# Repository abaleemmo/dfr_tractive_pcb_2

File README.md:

This project was made in fall 2026. It was made for Dallas Formula Racing, The formula SAE team based at The University of Texas at Dallas. It was made as a part of the embedded onboarding. 

See Tractive System Status Indicator w_ two boards & firmware.pdf for the project definition.

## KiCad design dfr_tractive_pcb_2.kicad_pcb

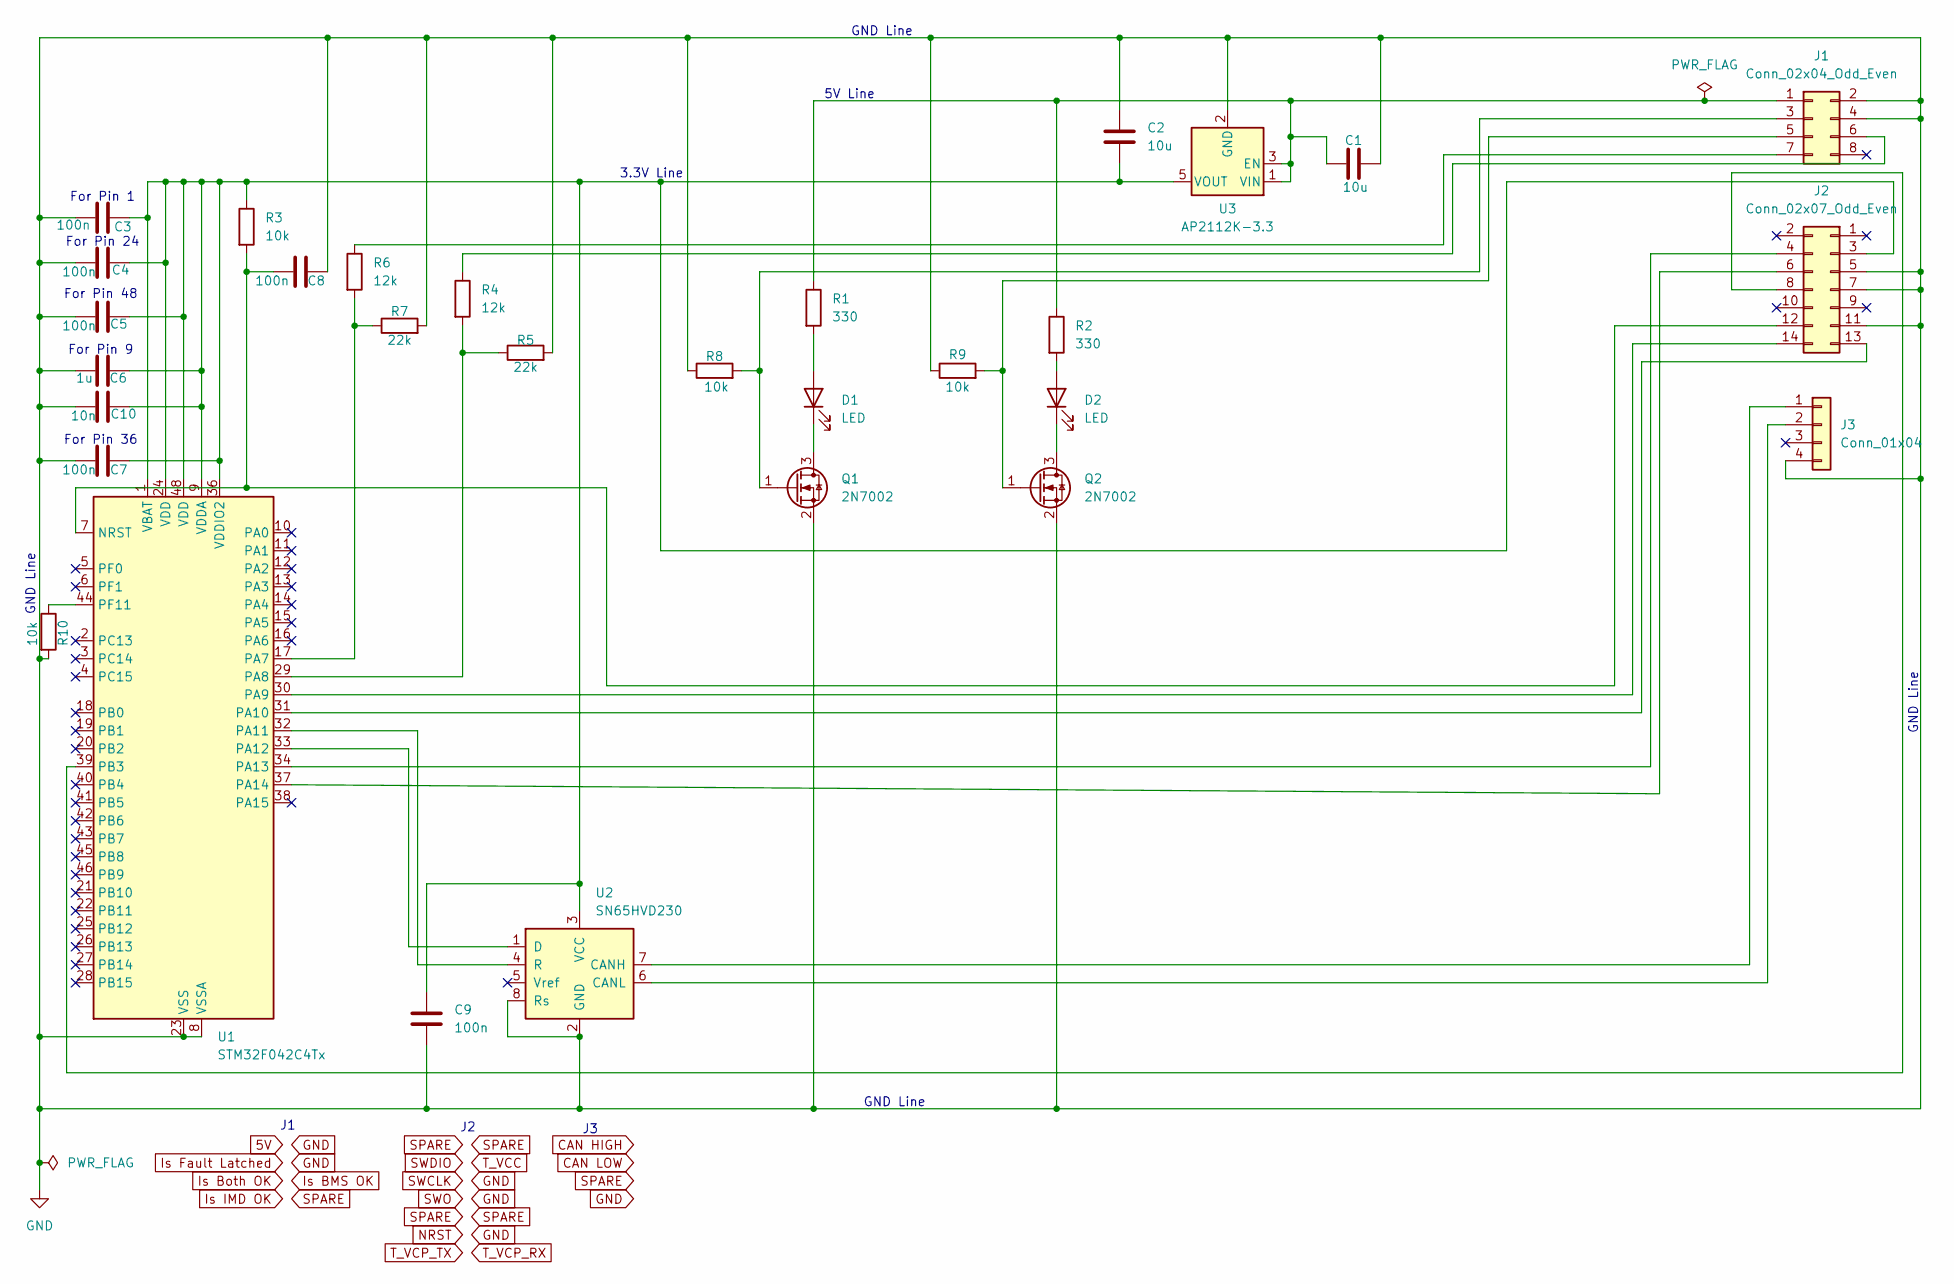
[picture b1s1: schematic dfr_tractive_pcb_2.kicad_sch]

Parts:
C1, C2: 10u; C_0805_2012Metric
C3, C4, C5, C7, C8, C9: 100n; C_0805_2012Metric
C6: 1u; C_0805_2012Metric
C10: 10n; C_0805_2012Metric
D1, D2: LED; LED_1206_3216Metric
J1: Conn_02x04_Odd_Even; PinSocket_2x04_P2.54mm_Vertical_SMD
J2: Conn_02x07_Odd_Even; SAMTEC_SHF-107-01-L-D-SM
J3: Conn_01x04; PinSocket_1x04_P2.54mm_Vertical_SMD_Pin1Right
Q1, Q2: 2N7002; SOT-23
R1, R2: 330; R_0805_2012Metric
R3, R8, R9, R10: 10k; R_0805_2012Metric
R4, R6: 12k; R_0805_2012Metric
R5, R7: 22k; R_0805_2012Metric
U1: STM32F042C4Tx; LQFP-48_7x7mm_P0.5mm
U2: SN65HVD230; SOIC-8_3.9x4.9mm_P1.27mm
U3: AP2112K-3.3; SOT-23-5

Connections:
GND: C1.1, C2.1, C3.2, C4.1, C5.1, C6.1, C7.2, C8.1, C9.2, C10.2, J1.2, J1.4, J2.5, J2.7, J2.11, J3.4, Q1.2 (S), Q2.2 (S), R5.2, R7.2, R8.1, R9.1, R10.2, U1.8 (VSSA), U1.23 (VSS), U1.35 (VSS), U1.47 (VSS), U2.2 (GND), U2.8 (Rs), U3.2 (GND)
unnamed: D1.2 (A), R1.2
unnamed: D1.1 (K), Q1.3 (D)
unnamed: D2.2 (A), R2.2
unnamed: D2.1 (K), Q2.3 (D)
unnamed: C1.2, J1.1, R1.1, R2.1, U3.1 (VIN), U3.3 (EN)
unnamed: J1.3, Q1.1 (G), R8.2
unnamed: J1.5, Q2.1 (G), R9.2
unnamed: J1.6, R4.1
unnamed: J1.7, R6.1
unnamed: C2.2, C3.1, C4.2, C5.2, C6.2, C7.1, C9.1, C10.1, J2.3, R3.1, U1.1 (VBAT), U1.9 (VDDA), U1.24 (VDD), U1.36 (VDDIO2), U1.48 (VDD), U2.3 (VCC), U3.5 (VOUT)
unnamed: J2.4, U1.34 (PA13)
unnamed: J2.6, U1.37 (PA14)
unnamed: J2.8, U1.39 (PB3)
unnamed: C8.2, J2.12, R3.2, U1.7 (NRST)
unnamed: J2.13, U1.31 (PA10)
unnamed: J2.14, U1.30 (PA9)
unnamed: J3.1, U2.7 (CANH)
unnamed: J3.2, U2.6 (CANL)
unnamed: R6.2, R7.1, U1.17 (PA7)
unnamed: R4.2, R5.1, U1.29 (PA8)
unnamed: U1.32 (PA11), U2.4 (R)
unnamed: U1.33 (PA12), U2.1 (D)
unnamed: R10.1, U1.44 (PF11)

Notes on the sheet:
GND Line
5V Line
3.3V Line
For Pin 36
For Pin 48
For Pin 24
For Pin 9
For Pin 1

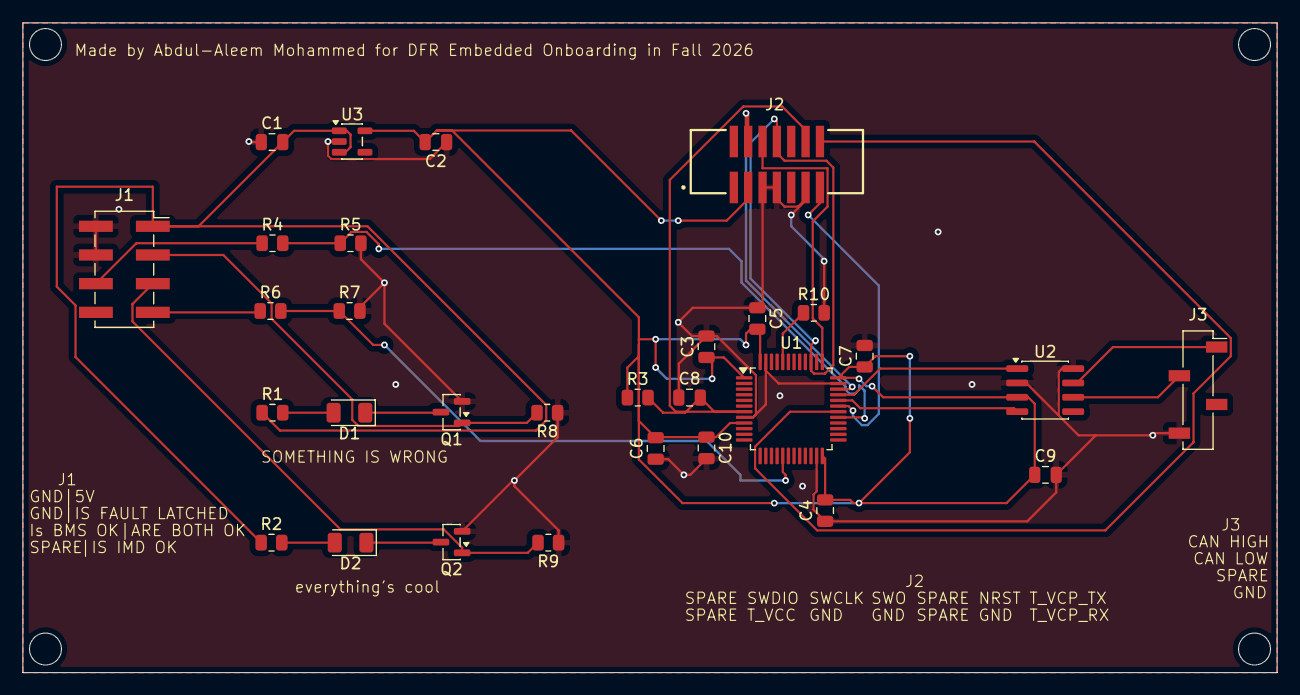
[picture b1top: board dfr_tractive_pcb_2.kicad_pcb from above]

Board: 2 copper layers, 111.0 x 57.5 mm, 30 parts (0 on the bottom side), 24 nets.
